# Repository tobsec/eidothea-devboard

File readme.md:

# EIDOTHEA DEVBOARD

The **Eidothea DevBoard** is designed for testing and development, compatible with the [Eidothea Board](https://github.com/tobsec/eidothea). It can be used both on a test bench and within an engine setup.

## Hardware Features

### Connectors

- **Sicma 56 Connector**: A weatherproof connector available on [AliExpress](https://aliexpress.com/item/32857771975.html).
- **Connector with 20cm Wiring Harness**: This is available for connecting to the Eidothea Board, also on [AliExpress](https://aliexpress.com/item/1005007332736311.html).

### Connectivity

- **2x CAN Bus Ports**: Available via SubD9 connectors (120Ω selectable).
- **Engine Connections**: All engine connections can be interrupted or disconnected as needed.
- **Pin Headers**: All signals are available on pin headers for easy probing or signal injection.

### Features

- **Ignition Toggle Switch**: For bench testing purposes.
- **Main Power Relay**: For controlling power during testing.
- **Analog Channel Emulation**: Analog channels can be emulated using potentiometers for simulation.

## Pinout
| No. | Pin                   | Description                | IN / OUT | Function                |
|-----|-----------------------|----------------------------|----------|-------------------------|
| 1   | IGN1                  | Ignition Trigger 1         | OUT      | Gate Driver IC          |
| 2   | IGN2                  | Ignition Trigger 2         | OUT      | Gate Driver IC          |
| 3   | IGN3                  | Ignition Trigger 3         | OUT      | Gate Driver IC          |
| 4   | IGN4                  | Ignition Trigger 4         | OUT      | Gate Driver IC          |
| 5   | IGN5                  | Ignition Trigger 5         | OUT      | Gate Driver IC          |
| 6   | IGN6                  | Ignition Trigger 6         | OUT      | Gate Driver IC          |
| 7   | IGN7                  | Ignition Trigger 7         | OUT      | Gate Driver IC          |
| 8   | IGN8                  | Ignition Trigger 8         | OUT      | Gate Driver IC          |
| 9   | GND                   | GND                        | IN       | Supply                  |
| 10  | GND                   | GND                        | IN       | Supply                  |
| 11  | GND                   | GND                        | IN       | Supply                  |
| 12  | DIGITAL_3             | Start Switch/Button Signal | IN       | Digital In 12V          |
| 13  | DIGITAL_VR_1          | Crank Sensor               | IN       | HALL / VR In            |
| 14  | DIGITAL_VR_4          | Cam Sensor                 | IN       | HALL / VR In            |
| 15  | LS4                   | Injector 4                 | OUT      | Low Side Switch         |
| 16  | LS3                   | Injector 3                 | OUT      | Low Side Switch         |
| 17  | LS2                   | Injector 2                 | OUT      | Low Side Switch         |
| 18  | LS1                   | Injector 1                 | OUT      | Low Side Switch         |
| 19  | LS9                   | Spare (e.g. Boost Control) | OUT      | Low Side Switch         |
| 20  | LS10                  | Main Relay Drive           | OUT      | Low Side Switch         |
| 21  | GND                   | Knock Sensor 2 -           | IN       | Knock Sensing           |
| 22  | LS5                   | Injector 5                 | OUT      | Low Side Switch         |
| 23  | LS6                   | Injector 6                 | OUT      | Low Side Switch         |
| 24  | LS7                   | Injector 7                 | OUT      | Low Side Switch         |
| 25  | LS8                   | Injector 8                 | OUT      | Low Side Switch         |
| 26  | 12V_RAW (+ DIGITAL_2) | Ignition (KL15)            | IN       | Supply                  |
| 27  | ETB1-                 | ETB M- / Idle Stepper A2   | OUT      | H Bridge (opt. Stepper) |
| 28  | ETB1+                 | ETB M+ / Idle Stepper A1   | OUT      | H Bridge (opt. Stepper) |
| 29  | CAN+                  | CAN1 H                     | IN / OUT | O2 Sensor CAN (500kbps) |
| 30  | CAN-                  | CAN1 L                     | IN / OUT | O2 Sensor CAN (500kbps) |
| 31  | CAN2+                 | CAN2 H                     | IN / OUT | NMEA2000 CAN (250kbps)  |
| 32  | CAN2-                 | CAN2 L                     | IN / OUT | NMEA2000 CAN (250kbps)  |
| 33  | KNOCK_2               | Knock Sensor 2 +           | IN       | Knock Sensing           |
| 34  | AT1                   | Water Temperature Sensor   | IN       | Analog Temp             |
| 35  | AV9                   | PPS2 (Idle Stepper B2)     | IN (OUT) | Analog  (opt. Stepper)  |
| 36  | AV8                   | PPS1 (Idle Stepper B1)     | IN (OUT) | Analog  (opt. Stepper)  |
| 37  | AV6                   | ETB TPS2                   | IN       | Analog Voltage          |
| 38  | AV3                   | Water Pressure Sensor      | IN       | Analog Voltage          |
| 39  | AV5                   | ETB TPS1                   | IN       | Analog Voltage          |
| 40  | LS11_F                | Tacho Out                  | OUT      | Low Side + PullUp       |
| 41  | LS15_F                | Starter Relay Drive        | OUT      | Low Side Switch         |
| 42  | LS13_F                | ~Main Relay Drive~ Spare   | OUT      | Low Side Switch         |
| 43  | 12V_MR                | Power (from Main Relay)    | IN       | Supply                  |
| 44  | 12V_MR                | Power (from Main Relay)    | IN       | Supply                  |
| 45  | 5V_SENSOR_1           | Sensor Supply 5V           | OUT      | Analog Supply 150mA     |
| 46  | GND                   | Sensor GND                 | OUT      | Analog GND              |
| 47  | KNOCK_1               | Knock Sensor 1 +           | IN       | Knock Sensing           |
| 48  | GND                   | Knock Sensor 1 -           | IN       | Knock Sensing           |
| 49  | AT2                   | Oil Temperature Sensor     | IN       | Analog Temp             |
| 50  | AV7                   | Fuel Pressure Sensor       | IN       | Analog Voltage          |
| 51  | AV2                   | IAT Sensor                 | IN       | Analog ~Voltage~ Temp   |
| 52  | AV4                   | Oil Pressure Sensor        | IN       | Analog Voltage          |
| 53  | AV1                   | MAP Sensor                 | IN       | Analog Voltage          |
| 54  | LS12_F                | Audio Warning Horn / MIL   | OUT      | Low Side Switch         |
| 55  | LS16_F                | Fuel Pump Relay Drive      | OUT      | Low Side Switch         |
| 56  | LS14_F                | Spare (e.g. Boost Control) | OUT      | Low Side Switch         |

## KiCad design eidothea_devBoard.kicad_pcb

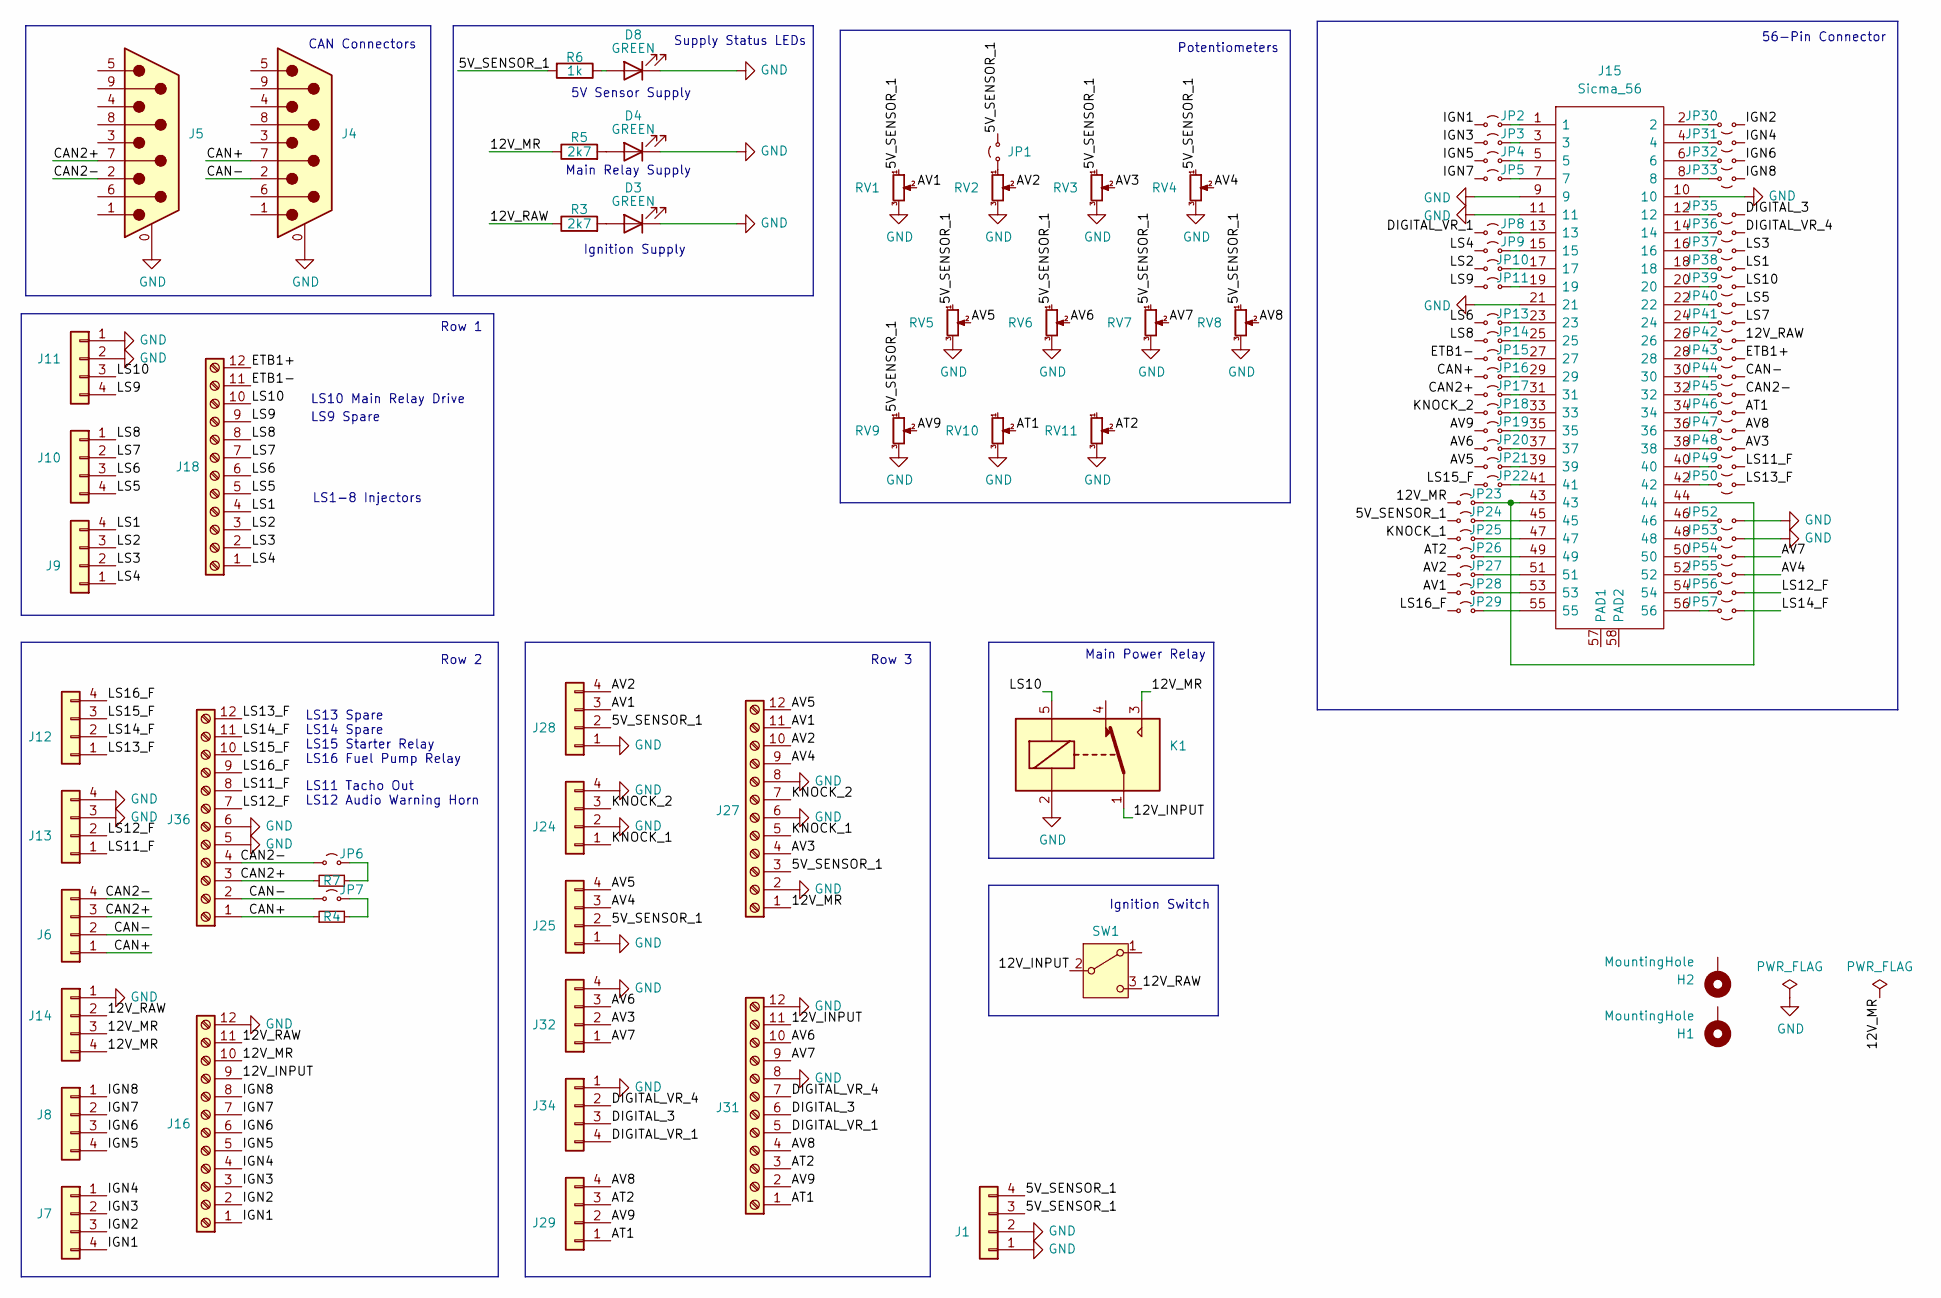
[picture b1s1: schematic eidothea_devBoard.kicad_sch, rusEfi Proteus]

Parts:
D3, D4, D8: GREEN; LED_0603_1608Metric; LCSC C72043
H1, H2: MountingHole; MountingHole_4mm_Pad_Via
J1, J6, J7, J8, J9, J10, J11, J12, J13, J14, J24, J25, J28, J29, J32, J34: Conn_01x01; PinHeader_1x04_P2.54mm_Vertical; LCSC N/A
J4, J5: DE9_Plug_MountingHoles; DSUB-9_Female_Vertical_P2.77x2.84mm_MountingHoles
J15: Sicma_56; Manufacturer_Part_Number 211PL562L0011
J16, J18, J27, J31, J36: Screw_Terminal_01x04; TerminalBlock_RND_205-00011_1x12_P5.00mm_Horizontal
JP1: Jumper_2_Bridged; SolderJumper-2_P1.3mm_Open_RoundedPad1.0x1.5mm
JP2, JP3, JP4, JP5, JP6, JP7, JP8, JP9, JP10, JP11, JP13, JP14, JP15, JP16, JP17, JP18, JP19, JP20, JP21, JP22, JP23, JP24, JP25, JP26, JP27, JP28, JP29, JP30, JP31, JP32, JP33, JP35, JP36, JP37, JP38, JP39, JP40, JP41, JP42, JP43, JP44, JP45, JP46, JP47, JP48, JP49, JP50, JP52, JP53, JP54, JP55, JP56, JP57: Jumper_2_Bridged; PinHeader_1x02_P2.54mm_Vertical
K1: SANYOU_SRD_Form_C; Relay_SPDT_SANYOU_SRD_Series_Form_C
R3, R5: 2k7; R_0805_2012Metric; LCSC C138017
R4, R7: R_Small; R_0805_2012Metric
R6: 1k; R_0805_2012Metric; LCSC C11702
RV1, RV2, RV3, RV4, RV5, RV6, RV7, RV8, RV9, RV10, RV11: R_Potentiometer_Small; Potentiometer_Alps_RK09K_Single_Vertical
SW1: SW_SPDT; SW_Toggle_Blue_wSlots

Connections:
/5V_SENSOR_1: J1.3, J1.4, J25.2, J27.3, J28.2, JP1.2 (B), JP24.1 (A), R6.2, RV1.1, RV3.1, RV4.1, RV5.1, RV6.1, RV7.1, RV8.1, RV9.1
/12V_INPUT: J16.9, J31.11, K1.1, SW1.2 (B)
/12V_MR: J14.3, J14.4, J16.10, J27.1, JP23.1 (A), K1.3, R5.1
/12V_RAW: J14.2, J16.11, JP42.1 (A), R3.1, SW1.3 (C)
/AT1: J29.1, J31.1, JP46.1 (A), RV10.2
/AT2: J29.3, J31.3, JP26.1 (A), RV11.2
/AV1: J27.11, J28.3, JP28.1 (A), RV1.2
/AV2: J27.10, J28.4, JP27.1 (A), RV2.2
/AV3: J27.4, J32.2, JP48.1 (A), RV3.2
/AV4: J25.3, J27.9, JP55.1 (A), RV4.2
/AV5: J25.4, J27.12, JP21.1 (A), RV5.2
/AV6: J31.10, J32.3, JP20.1 (A), RV6.2
/AV7: J31.9, J32.1, JP54.1 (A), RV7.2
/AV8: J29.4, J31.4, JP47.1 (A), RV8.2
/AV9: J29.2, J31.2, JP19.1 (A), RV9.2
/CAN2+: J5.7, J6.3, J36.3, JP17.1 (A), R7.1
/CAN2-: J5.2, J6.4, J36.4, JP6.1 (A), JP45.1 (A)
/CAN+: J4.7, J6.1, J36.1, JP16.1 (A), R4.1
/CAN-: J4.2, J6.2, J36.2, JP7.1 (A), JP44.1 (A)
/DIGITAL_3: J31.6, J34.3, JP35.1 (A)
/DIGITAL_VR_1: J31.5, J34.4, JP8.1 (A)
/DIGITAL_VR_4: J31.7, J34.2, JP36.1 (A)
/ETB1+: J18.12, JP43.1 (A)
/ETB1-: J18.11, JP15.1 (A)
/IGN1: J7.4, J16.1, JP2.1 (A)
/IGN2: J7.3, J16.2, JP30.1 (A)
/IGN3: J7.2, J16.3, JP3.1 (A)
/IGN4: J7.1, J16.4, JP31.1 (A)
/IGN5: J8.4, J16.5, JP4.1 (A)
/IGN6: J8.3, J16.6, JP32.1 (A)
/IGN7: J8.2, J16.7, JP5.1 (A)
/IGN8: J8.1, J16.8, JP33.1 (A)
/KNOCK_1: J24.1, J27.5, JP25.1 (A)
/KNOCK_2: J24.3, J27.7, JP18.1 (A)
/LS1: J9.4, J18.4, JP38.1 (A)
/LS2: J9.3, J18.3, JP10.1 (A)
/LS3: J9.2, J18.2, JP37.1 (A)
/LS4: J9.1, J18.1, JP9.1 (A)
/LS5: J10.4, J18.5, JP40.1 (A)
/LS6: J10.3, J18.6, JP13.1 (A)
/LS7: J10.2, J18.7, JP41.1 (A)
/LS8: J10.1, J18.8, JP14.1 (A)
/LS9: J11.4, J18.9, JP11.1 (A)
/LS10: J11.3, J18.10, JP39.1 (A), K1.5
/LS11_F: J13.1, J36.8, JP49.1 (A)
/LS12_F: J13.2, J36.7, JP56.1 (A)
/LS13_F: J12.1, J36.12, JP50.1 (A)
/LS14_F: J12.2, J36.11, JP57.1 (A)
/LS15_F: J12.3, J36.10, JP22.1 (A)
/LS16_F: J12.4, J36.9, JP29.1 (A)
GND: D3.1 (K), D4.1 (K), D8.1 (K), J1.1, J1.2, J4.0 (PAD), J5.0 (PAD), J11.1, J11.2, J13.3, J13.4, J14.1, J15.9, J15.10, J15.11, J15.21, J16.12, J24.2, J24.4, J25.1, J27.2, J27.6, J27.8, J28.1, J31.8, J31.12, J32.4, J34.1, J36.5, J36.6, JP52.1 (A), JP53.1 (A), K1.2, RV1.3, RV2.3, RV3.3, RV4.3, RV5.3, RV6.3, RV7.3, RV8.3, RV9.3, RV10.3, RV11.3
unnamed: D3.2 (A), R3.2
unnamed: D4.2 (A), R5.2
unnamed: D8.2 (A), R6.1
unnamed: JP1.1 (A), RV2.1
unnamed: J15.1, JP2.2 (B)
unnamed: J15.3, JP3.2 (B)
unnamed: J15.5, JP4.2 (B)
unnamed: J15.7, JP5.2 (B)
unnamed: JP6.2 (B), R7.2
unnamed: JP7.2 (B), R4.2
unnamed: J15.13, JP8.2 (B)
unnamed: J15.15, JP9.2 (B)
unnamed: J15.17, JP10.2 (B)
unnamed: J15.19, JP11.2 (B)
unnamed: J15.23, JP13.2 (B)
unnamed: J15.25, JP14.2 (B)
unnamed: J15.27, JP15.2 (B)
unnamed: J15.29, JP16.2 (B)
unnamed: J15.31, JP17.2 (B)
unnamed: J15.33, JP18.2 (B)
unnamed: J15.35, JP19.2 (B)
unnamed: J15.37, JP20.2 (B)
unnamed: J15.39, JP21.2 (B)
unnamed: J15.41, JP22.2 (B)
unnamed: J15.43, J15.44, JP23.2 (B)
unnamed: J15.45, JP24.2 (B)
unnamed: J15.47, JP25.2 (B)
unnamed: J15.49, JP26.2 (B)
unnamed: J15.51, JP27.2 (B)
unnamed: J15.53, JP28.2 (B)
unnamed: J15.55, JP29.2 (B)
unnamed: J15.2, JP30.2 (B)
unnamed: J15.4, JP31.2 (B)
unnamed: J15.6, JP32.2 (B)
unnamed: J15.8, JP33.2 (B)
unnamed: J15.12, JP35.2 (B)
unnamed: J15.14, JP36.2 (B)
unnamed: J15.16, JP37.2 (B)
unnamed: J15.18, JP38.2 (B)
unnamed: J15.20, JP39.2 (B)
unnamed: J15.22, JP40.2 (B)
unnamed: J15.24, JP41.2 (B)
unnamed: J15.26, JP42.2 (B)
unnamed: J15.28, JP43.2 (B)
unnamed: J15.30, JP44.2 (B)
unnamed: J15.32, JP45.2 (B)
unnamed: J15.34, JP46.2 (B)
unnamed: J15.36, JP47.2 (B)
unnamed: J15.38, JP48.2 (B)
unnamed: J15.40, JP49.2 (B)
unnamed: J15.42, JP50.2 (B)
unnamed: J15.46, JP52.2 (B)
unnamed: J15.48, JP53.2 (B)
unnamed: J15.50, JP54.2 (B)
unnamed: J15.52, JP55.2 (B)
unnamed: J15.54, JP56.2 (B)
unnamed: J15.56, JP57.2 (B)

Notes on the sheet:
Ignition Switch
LS9 Spare
LS1-8 Injectors
Supply Status LEDs
Row 1
Main Power Relay
56-Pin Connector
CAN Connectors
LS10 Main Relay Drive
LS13 Spare LS14 Spare LS15 Starter Relay LS16 Fuel Pump Relay
Main Relay Supply
Row 2
LS11 Tacho Out LS12 Audio Warning Horn
Potentiometers
Row 3
Ignition Supply
5V Sensor Supply

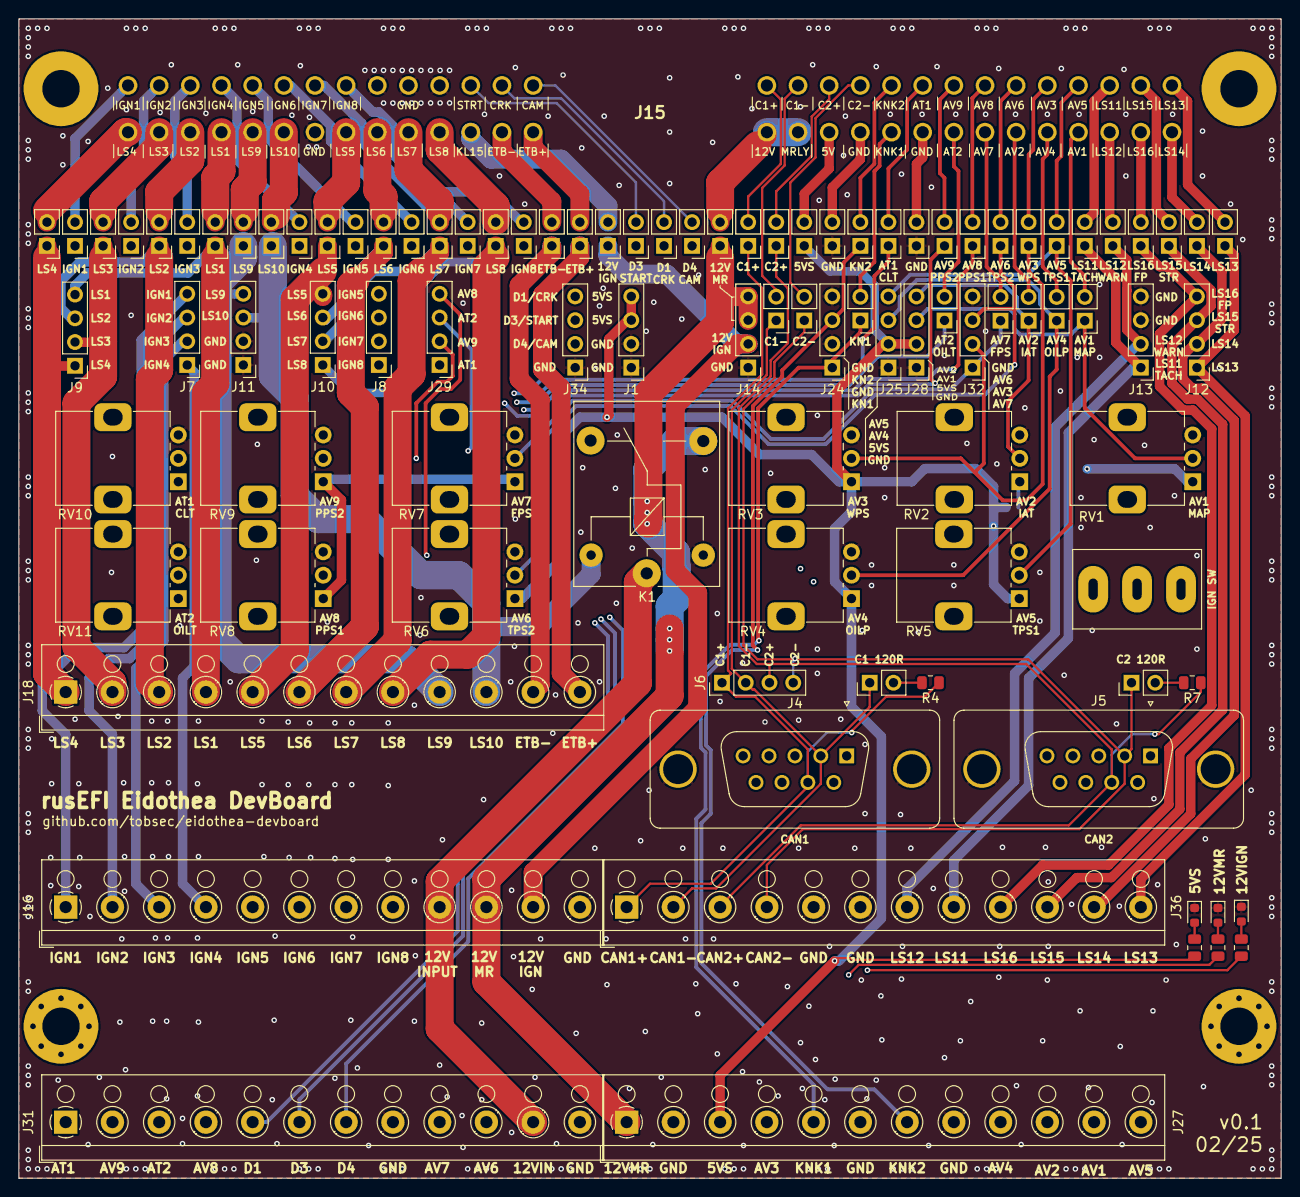
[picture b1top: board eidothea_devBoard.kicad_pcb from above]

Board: 4 copper layers, 135.0 x 124.0 mm, 101 parts (1 on the bottom side), 108 nets.

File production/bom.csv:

Designator,Footprint,Quantity,Value,LCSC Part #
"D3, D4, D8",0603,3,GREEN,C72043
"J1, J10, J11, J12, J13, J14, J24, J25, J28, J29, J32, J34, J6, J7, J8, J9",PinHeader_1x04_P2.54mm_Vertical,16,Conn_01x01,N/A
"J16, J18, J27, J31, J36",TerminalBlock_RND_205-00011_1x12_P5.00mm_Horizontal,5,Screw_Terminal_01x04,
"J4, J5",DSUB-9_Female_Vertical_P2.77x2.84mm_MountingHoles,2,DE9_Plug_MountingHoles,
JP1,SolderJumper-2_P1.3mm_Open_RoundedPad1.0x1.5mm,1,Jumper_2_Bridged,
"JP10, JP11, JP13, JP14, JP15, JP16, JP17, JP18, JP19, JP2, JP20, JP21, JP22, JP23, JP24, JP25, JP26, JP27, JP28, JP29, JP3, JP30, JP31, JP32, JP33, JP35, JP36, JP37, JP38, JP39, JP4, JP40, JP41, JP42, JP43, JP44, JP45, JP46, JP47, JP48, JP49, JP5, JP50, JP52, JP53, JP54, JP55, JP56, JP57, JP6, JP7, JP8, JP9",PinHeader_1x02_P2.54mm_Vertical,53,Jumper_2_Bridged,
K1,Relay_SPDT_SANYOU_SRD_Series_Form_C,1,SANYOU_SRD_Form_C,
"R3, R5",0805,2,2k7,C138017
"R4, R7",0805,2,R_Small,
R6,0805,1,1k,C11702
"RV1, RV10, RV11, RV2, RV3, RV4, RV5, RV6, RV7, RV8, RV9",Potentiometer_Alps_RK09K_Single_Vertical,11,R_Potentiometer_Small,
SW1,SW_Toggle_Blue_wSlots,1,SW_SPDT,
